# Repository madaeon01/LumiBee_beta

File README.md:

# LumiBee_beta

This is a WIP project.
Here you can find:
-all the 3d printable parts as STL;
-all the non 3d printable parts;
-the PCB eagle files;
-the arduino firmware;
-the chitubox profiles;
-the Android APP beta. Note: the current app stores the PNGs in the app directly, so you must put all your layers in the
RES\drawables folder manually, then compile. I plan to implement the ability to select files from a folder 
from the App, but at the moment, all the LumiBee development (hardware, software, firmware, app and all the testing) is done by 
ONE single person (me) as a side project, for free. So feel free to contribute.

To do:
-complete BOM
-assembly instructions
-how to use the screen luminosity tester
-how to use - guide
-how to use the app
In the next days this guide wil be update so if you do not find some info, just write me.

A 3D viewable model of the assembly is available here:
https://sketchfab.com/3d-models/lumibee-43fde758bdf04565baee1a75a64f292f

You can contribute to this project with a donation to support it if you like it, with a paypal donation at madaeon@gmail.com

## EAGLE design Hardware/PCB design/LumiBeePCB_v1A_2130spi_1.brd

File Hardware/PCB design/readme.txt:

This is the last revision of the PCB design.

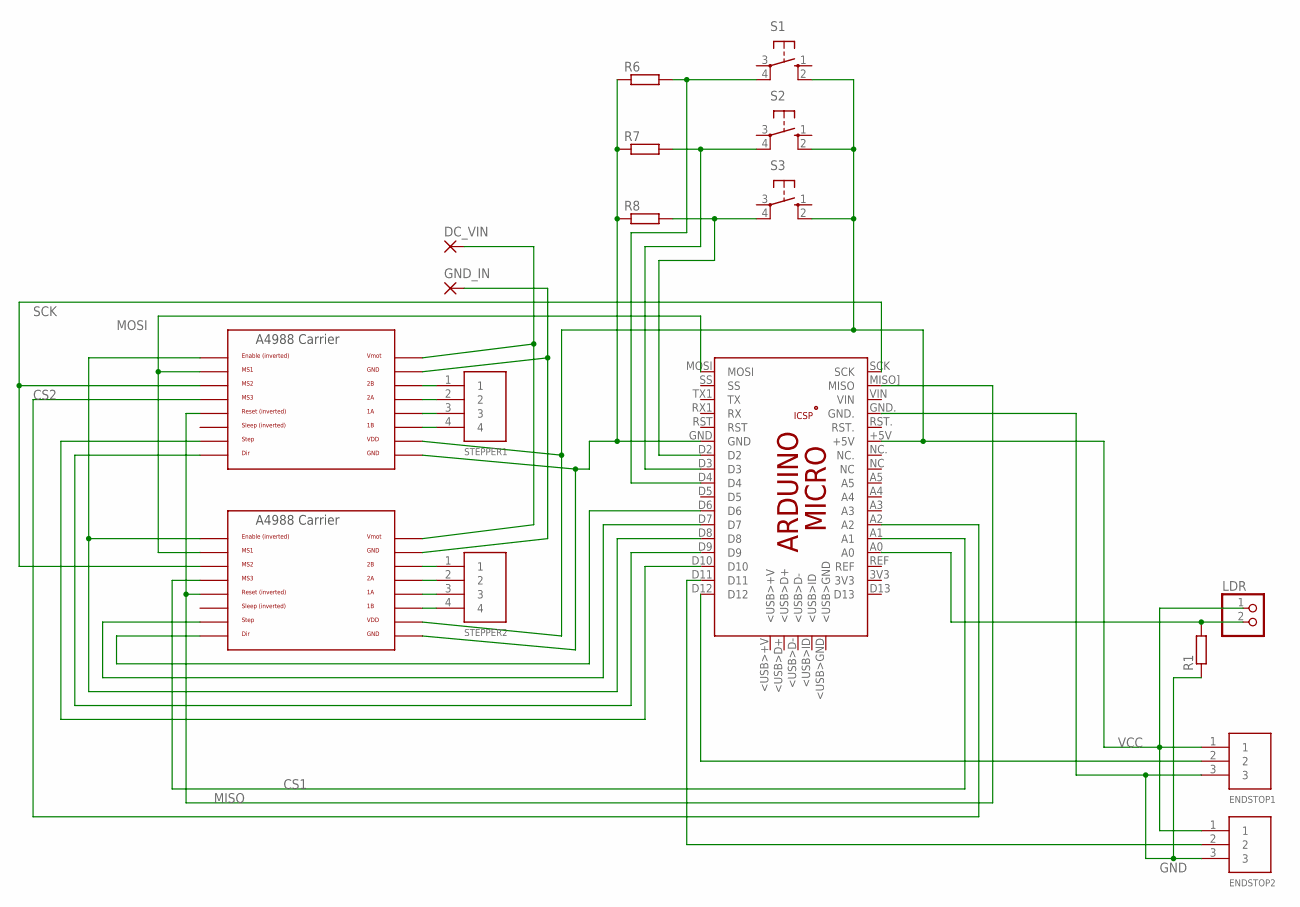
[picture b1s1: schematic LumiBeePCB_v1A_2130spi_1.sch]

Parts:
DC_VIN: 2,54/0,8
ENDSTOP1, ENDSTOP2: 3PIN; B3B-PH-K-S
GND_IN: 2,54/0,8
LDR: PINHD-1X2; 1X02
PCB1: ARDUINO_MICRO
R1, R6, R7, R8: R-EU_M1206; M1206
S1, S2, S3: 10-XX; B3F-10XX
STEPPER1, STEPPER2: 4PIN; B4B-PH-K-S
U$1, U$2: A4988BREAKOUT

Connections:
CS1: PCB1.A1, U$2.MS3
CS2: PCB1.A2, U$1.MS3
GND: ENDSTOP1.3, ENDSTOP2.3, PCB1.GND., R1.1
MISO: PCB1.MISO] (MISO), U$1.RST, U$2.RST
MOSI: PCB1.MOSI, U$1.MS1, U$2.MS1
unnamed: GND_IN.1, U$1.GND, U$2.GND
unnamed: DC_VIN.1, U$1.VMOT, U$2.VMOT
unnamed: STEPPER1.1, U$1.2B
unnamed: PCB1.GND, R6.1, R7.1, R8.1, U$1.GND@0 (GND), U$2.GND@0 (GND)
unnamed: ENDSTOP1.2, PCB1.D12
unnamed: STEPPER1.2, U$1.2A
unnamed: STEPPER1.3, U$1.1A
unnamed: STEPPER1.4, U$1.1B
unnamed: STEPPER2.1, U$2.2B
unnamed: STEPPER2.2, U$2.2A
unnamed: STEPPER2.3, U$2.1A
unnamed: STEPPER2.4, U$2.1B
unnamed: ENDSTOP2.2, PCB1.D11
unnamed: PCB1.D10, U$1.STEP
unnamed: PCB1.D9, U$1.DIR
unnamed: PCB1.D8, U$1.EN, U$2.EN
unnamed: PCB1.D7, U$2.STEP
unnamed: PCB1.D6, U$2.DIR
unnamed: LDR.2, PCB1.A0, R1.2
unnamed: PCB1.D2, R8.2, S3.4 (P1)
unnamed: PCB1.D3, R7.2, S2.4 (P1)
unnamed: PCB1.D4, R6.2, S1.4 (P1)
SCK: PCB1.SCK, U$1.MS2, U$2.MS2
VCC: ENDSTOP1.1, ENDSTOP2.1, LDR.1, PCB1.+5V, S1.2 (S1), S2.2 (S1), S3.2 (S1), U$1.VDD, U$2.VDD

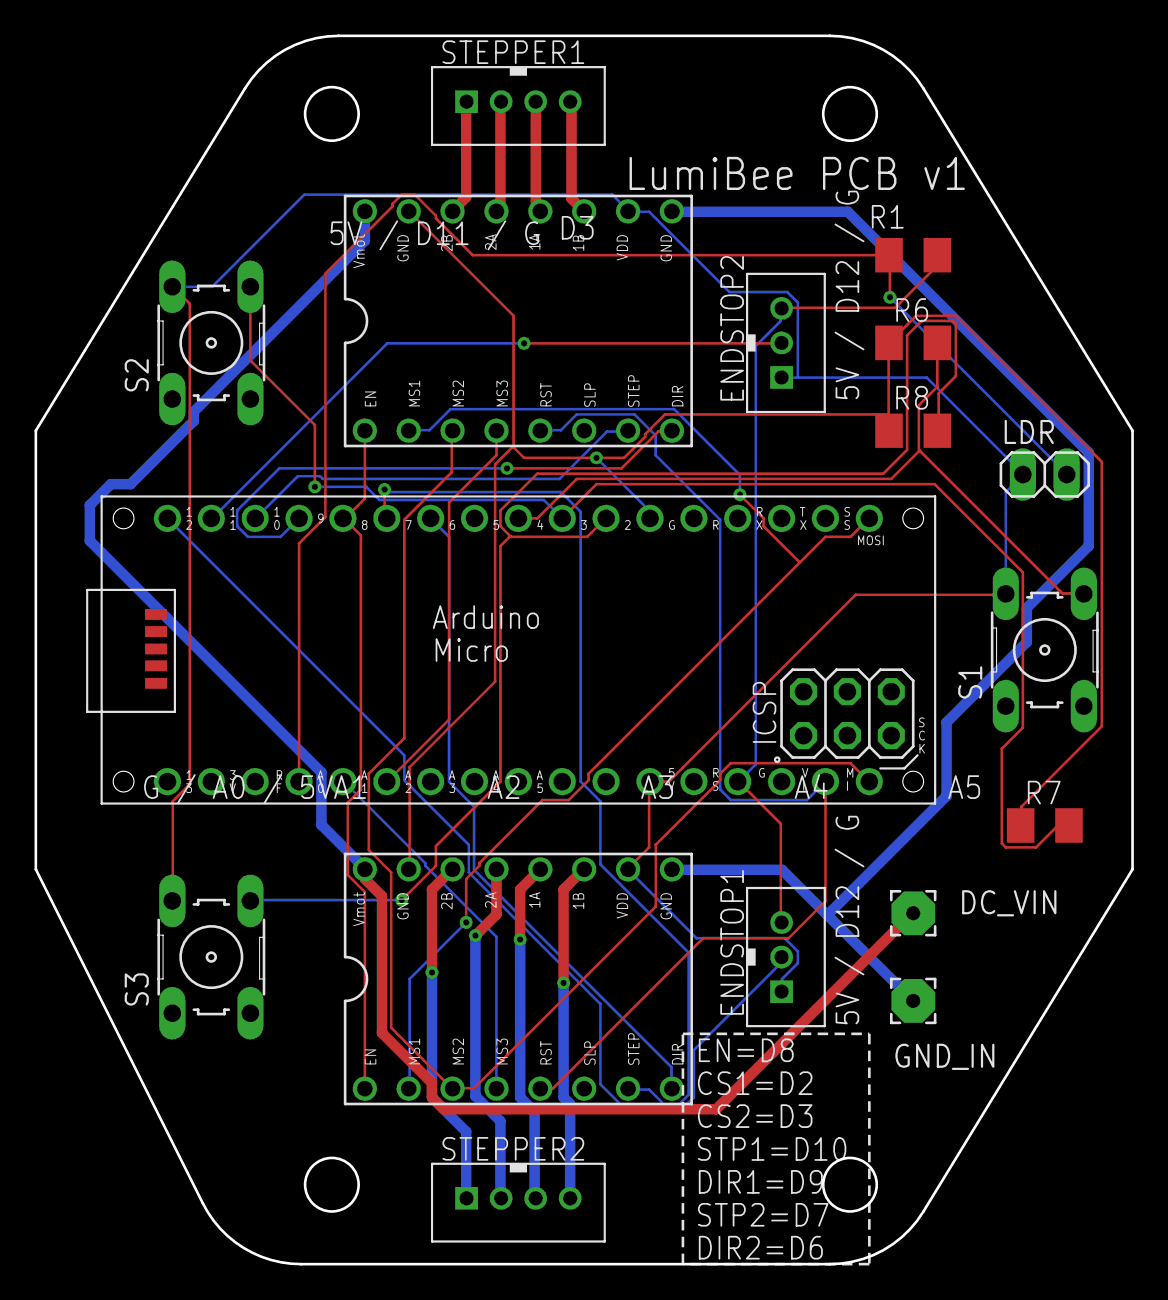
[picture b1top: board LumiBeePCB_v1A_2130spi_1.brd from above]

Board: 2 copper layers, 63.5 x 71.1 mm, 17 parts (0 on the bottom side), 29 nets.

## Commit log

2020-01-28 Add files via upload
    The entire LumiBee design in STEP file format.
2022-10-11 Archiving old files, uploading updated ones
2022-10-11 Putting the old files in archive
2022-10-11 Deleting old files
2022-10-11 Uploading newer files
    I exported these from the STEP file and made their names match the old ones. I'm not sure how many of them have changed from the previous version, figured it'd be safer to do all of them.
